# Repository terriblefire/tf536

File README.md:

# TF536

A Motorola 68030-based hardware accelerator for Amiga 500 and CDTV computers. The TF536 provides a modern 68030 CPU upgrade with SDRAM expansion, IDE interface, and custom CPLD logic for bus arbitration and peripheral management.

**Note**: For Atari ST systems, see the ST536 derivative available from [Exxos](https://www.exxosforum.co.uk/).

## Discord

https://discord.gg/Q5zfusgnmH

## Overview

The TF536 is an open-source hardware accelerator that replaces the original 68000 CPU in Amiga 500 and CDTV systems with a faster 68030 processor. The design uses a Xilinx XC95144XL/XC95288XL CPLD to implement:

- Bus arbitration between 68030 and host system
- SDRAM controller with Amiga autoconfig support
- IDE/ATA interface (Amiga Gayle chipset emulation)
- 68000 peripheral bus timing (6800-style VPA/VMA)
- Clock generation and speed control
- Interrupt handling and bus error generation

## Features

- **68030 CPU**: Significant performance upgrade from stock 68000
- **SDRAM Expansion**: Up to 128MB of fast RAM via SDRAM controller
- **IDE Interface**: Connect IDE hard drives and CF card adapters
- **Amiga Autoconfig**: Automatic memory configuration (Zorro-II compatible)
- **Multi-Platform**: Support for Amiga 500 and CDTV
- **Boot ROM**: Custom 68k assembly boot code with color cycling demo
- **Hardware Revisions**: Evolution from Rev 1 to Rev 2 with improvements
- **Automated Manufacturing**: Complete Gerber, BOM, and CPL generation

## Supported Platforms

The TF536 firmware supports two different target platforms, selected at compile time:

- **A500**: Amiga 500 configuration
- **CDTV**: Commodore CDTV configuration (different ROM decode)

Each platform has specific CPLD defines (`A500`, `CDTV`) that customize the memory map and bus interface behavior.

## Hardware Revisions

### Revision 2 (Current)
The current repository contains the **Rev 2** design (`boards/tf536r2/`), which includes:
- 4-layer PCB design
- Improved signal integrity
- JLCPCB-compatible manufacturing outputs
- Both top and bottom component placement
- Configurable IDE interface (buffered or unbuffered)

### Revision 1
Legacy design available in `boards/tf536r1/` with earlier schematic iterations.

## IDE Interface Build Options

The TF536 supports two mutually exclusive IDE interface configurations:

- **Unbuffered (Default)**: Populate RN5-RN10 with 0Ω resistor networks
- **Buffered**: Populate IC4, IC5, IC6 with buffer ICs

⚠️ **Important**: Do not populate both options simultaneously.

See [IDE_BUILD_OPTIONS.md](IDE_BUILD_OPTIONS.md) for detailed information on choosing and assembling the appropriate configuration.

## Repository Structure

```
tf536/
├── rtl/                    # Verilog RTL source code
│   ├── main_top.v         # Top-level CPLD module (parametric)
│   ├── clocks.v           # Clock generation and CPU speed control
│   ├── sdram.v            # SDRAM controller with burst support
│   ├── sdram_init.v       # SDRAM initialization state machine
│   ├── autoconfig.v       # Amiga Zorro-II autoconfiguration
│   ├── bus.v              # Bus delay and arbitration logic
│   ├── m6800.v            # Motorola 6800 peripheral bus timing
│   ├── ata.v              # IDE/ATA interface controller
│   ├── gayle.v            # Amiga Gayle IDE chipset emulation
│   ├── interrupt.v        # Interrupt level management
│   ├── intreqr.v          # Interrupt request register patching
│   └── bootrom.v          # Boot ROM (auto-generated from assembly)
├── rom/                    # Boot ROM assembly source
│   ├── bootrom.asm        # 68k assembly boot code
│   ├── bin2vrlg           # Binary to Verilog converter (Python 3)
│   └── Makefile           # ROM build automation
├── boards/                 # Board-specific build configurations
│   ├── tf536r1/           # Revision 1 board files
│   ├── tf536r2/           # Revision 2 board files (current)
│   │   ├── tf536r2_main_top.v  # Board-specific wrapper
│   │   ├── tf536r2_main.ucf    # Pin constraints
│   │   └── Makefile            # Build targets (a500, cdtv, atarist)
│   ├── Makefile.cpld      # Common CPLD synthesis rules
│   ├── Makefile.inc       # Docker/Xilinx environment setup
│   └── boards.txt         # List of board configurations
├── testsuite/             # Verilog testbenches
│   ├── bus/               # Bus interface tests
│   ├── interrupt/         # Interrupt handling tests
│   └── Makefile.inc       # Common test environment
├── eagle/                 # Eagle CAD hardware designs
│   ├── tf536.sch          # Schematic (3 sheets)
│   ├── tf536.brd          # PCB layout (4-layer)
│   ├── extract_bom.py     # BOM extraction (JLCPCB format)
│   ├── extract_cpl.py     # Component placement list
│   ├── jlcpcb_4_layer_v9.cam  # Gerber generation CAM job
│   └── Makefile           # Automated manufacturing outputs
└── .github/workflows/     # CI/CD automation
    ├── build-firmware.yml     # CPLD firmware builds
    ├── gerbers.yml            # Gerber file generation
    ├── schematic-pdf.yml      # PDF schematic generation
    └── generate_assembly.yml  # BOM and CPL generation
```

## Building the CPLD Firmware

### Prerequisites

- **Linux**: Xilinx ISE 10.1 installed at `/opt/Xilinx/10.1/`
- **macOS/Windows**: Docker (automatically uses terriblefire78/xilinx:v1 container)
- **68k Assembly**: vasmm68k_mot assembler for boot ROM

The build system automatically handles Docker on non-Linux platforms.

### Build Boot ROM

```bash
cd rom
make
```

Generates `bootrom.v` from `bootrom.asm` with embedded version string.

### Build All Platforms

```bash
cd boards/tf536r2
make
```

This compiles CPLD firmware for both platforms using the XC95288XL CPLD:
- `tf536r2_main_top_A500_XC95288XL_PHASE_7.jed` (Amiga 500)
- `tf536r2_main_top_CDTV_XC95288XL_PHASE_7.jed` (CDTV)

### Build Specific Platform

```bash
cd boards/tf536r2
make a500      # Amiga 500
make cdtv      # Commodore CDTV
```

Output: `.jed` (JEDEC programming files) and `.svf` (Serial Vector Format)

### Build Configuration

Key Makefile variables (used internally by `boards/tf536r2/Makefile`):

```makefile
CHIPSIZE=288        # XC95288XL CPLD
CLOCK_PHASE=7       # Clock phase alignment (0-7)
TARGET=A500         # Platform target (A500, CDTV)
```

### Clean Build Artifacts

```bash
cd boards
make clean       # Remove intermediate files, keep .jed
make distclean   # Remove all generated files including .jed
```

### Create Release Package

```bash
cd boards
make zip
```

Generates: `tf536_YYYY_MM_DD_<git-hash>.zip` containing all board `.jed` files.

## Hardware Manufacturing

### Generate Gerber Files

```bash
cd eagle
make gerbers
```

Output: `tf536_<git>_<date>.zip` containing complete 4-layer PCB fabrication package for JLCPCB.

### Generate PDF Schematic

```bash
cd eagle
make pdf
```

Output: `tf536_<git>_<date>.pdf` - Multi-page PDF schematic (3 sheets)

### Generate Assembly Files

```bash
cd eagle
make assembly
```

Generates:
- `tf536_bom.csv` - Bill of Materials (JLCPCB format)
- `tf536_cpl.csv` - Component Placement List for SMT assembly

### Complete Manufacturing Output

```bash
cd eagle
make all         # Gerber files + ZIP
make bom         # Bill of Materials only
make cpl         # Component Placement List only
make clean       # Remove all generated files
```

## RTL Architecture

### Module Hierarchy

**Top-level:** `main_top.v` (parametric, instantiated by board-specific wrapper)

**Key Modules:**
- **`clocks.v`**: Clock management, CPU speed control, 7MHz/100MHz domain crossing
- **`sdram.v`**: SDRAM controller with burst read/write, refresh, autoconfig decode
- **`sdram_init.v`**: SDRAM initialization (precharge, auto-refresh, mode register)
- **`autoconfig.v`**: Amiga Zorro-II autoconfiguration protocol
- **`bus.v`**: Bus delay state machine and control
- **`m6800.v`**: Motorola 6800 peripheral bus timing (VPA/VMA/E-clock)
- **`ata.v`**: IDE/ATA interface with wait state generation
- **`gayle.v`**: Amiga Gayle chipset emulation (IDE interrupt, status)
- **`interrupt.v`**: IPL interrupt level assertion and acknowledgment
- **`intreqr.v`**: INTREQ/INTENA register patching for IDE interrupts
- **`bootrom.v`**: Boot ROM lookup table (auto-generated from assembly)

### Design Patterns

- **Dual-clock design**: CLK7M (7MHz Amiga bus) and CLK100M (system/SDRAM)
- **Bus punting**: Decides when to drive Amiga bus vs. tri-state (HIGHZ)
- **Platform-specific compilation**: `ifdef` directives for A500/CDTV
- **DSACK protocol**: Variable wait state insertion for fast RAM access
- **Cache support**: CBREQ/CBACK/CIIN signals for 68030 cache control

### Memory Map

**Amiga Configuration:**
- `$00000000-$001FFFFF`: Chip RAM (host)
- `$00200000-$009FFFFF`: Autoconfig space
- `$00A00000-$00BFFFFF`: Reserved (CIA, Custom chips)
- `$00C00000-$00DFFFFF`: Slow RAM (host)
- `$00E00000-$00E7FFFF`: Autoconfig ROM
- `$00F00000-$00F7FFFF`: Cartridge ROM (unless CDTV)
- `$00F80000-$00FFFFFF`: System ROM (Kickstart)
- `$01000000+`: Fast RAM (SDRAM, autoconfigured)

**CDTV Configuration:**
- ROM decode disabled at `$00F00000` (see `main_top.v:268-272`)

## Testing

Run Verilog testbenches:

```bash
cd testsuite/interrupt
make

cd testsuite/bus
make
```

Testbenches use Icarus Verilog (iverilog) and follow naming convention `test_*.v`.

## Programming the CPLD

The `.jed` files can be programmed using:
- JTAG programmer (Xilinx Platform Cable, etc.)
- xc3sprog with FT232H-based programmer
- Xilinx iMPACT software

## CI/CD Automation

GitHub Actions automatically builds:
- **CPLD Firmware**: On changes to `rtl/`, `boards/`, or `rom/`
- **Gerber Files**: On push to develop/main branches
- **PDF Schematics**: On push to develop/main branches
- **Assembly Files**: On changes to Eagle files or extraction scripts

All build artifacts are uploaded and available for download for 90 days. Tagged releases automatically include manufacturing outputs.

## License

This work is licensed under the Creative Commons Attribution-NoDerivatives 4.0 International License.

Copyright (c) 2016-2025 Stephen J. Leary

You are free to:
- **Share** - copy and redistribute the material in any medium or format for any purpose, even commercially

Under the following terms:
- **Attribution** - You must give appropriate credit, provide a link to the license, and indicate if changes were made
- **NoDerivatives** - If you remix, transform, or build upon the material, you may not distribute the modified material

See the [LICENSE](LICENSE) file for the complete license text, or visit:
https://creativecommons.org/licenses/by-nd/4.0/

## Community

Join the TerribleFire Discord for support, discussions, and updates: https://discord.gg/aXGkKWJQ

## Credits

- Hardware design: Stephen Leary
- CPLD development: Stephen Leary
- Open source contributions welcome!

---

**Note**: This is a complex hardware project requiring experience with:
- Eagle CAD for hardware modifications
- Verilog HDL for CPLD changes
- 68000/68030 assembly for boot ROM modifications
- Xilinx ISE 10.1 toolchain for CPLD synthesis
- PCB fabrication and SMT assembly services

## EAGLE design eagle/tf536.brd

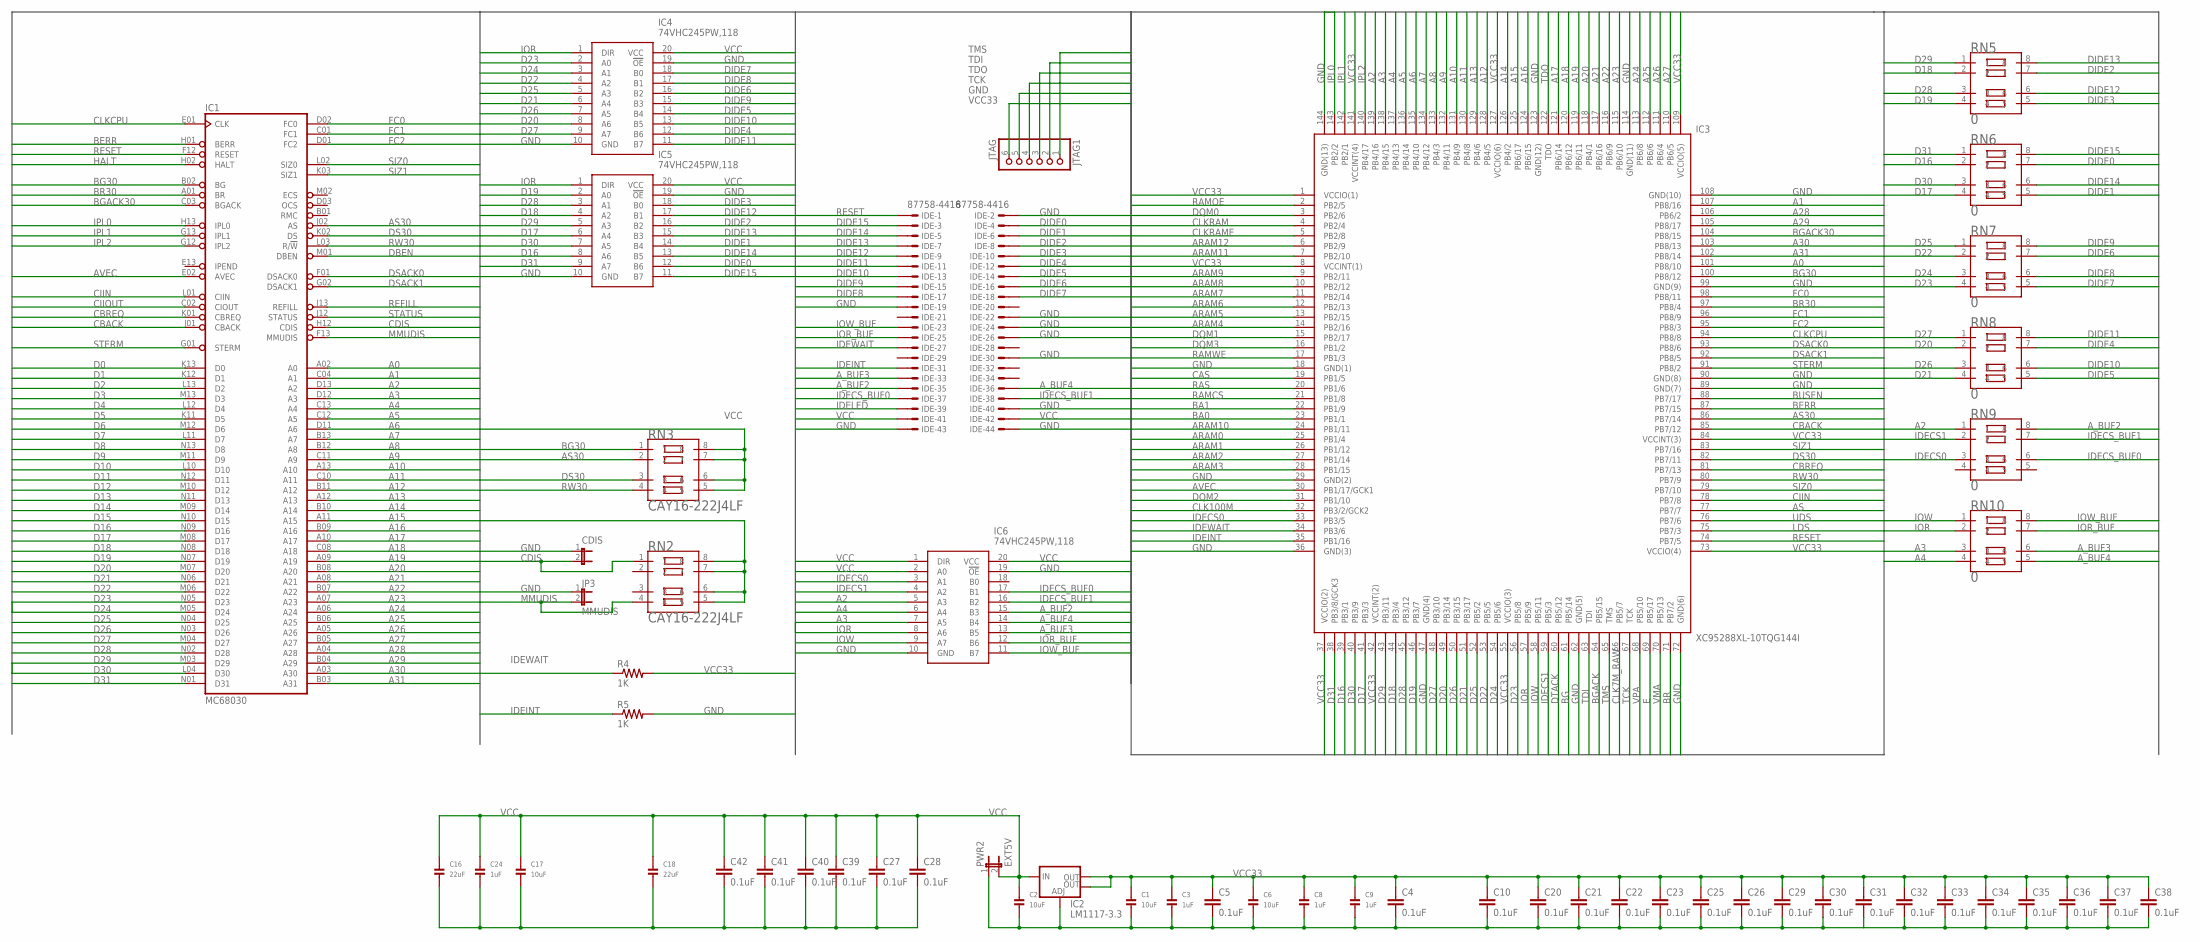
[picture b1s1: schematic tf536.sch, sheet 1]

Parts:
C1, C2, C6, C17: 10uF; 1206
C3, C8, C9, C24: 1uF; 1206
C4, C5, C10, C20, C21, C22, C23, C25, C26, C27, C28, C29, C30, C31, C32, C33, C34, C35, C36, C37, C38, C39, C40, C41, C42: 0.1uF; 0603-CAP
C16, C18: 22uF; 1206
IC1: MC68030; MPGA128
IC2: LM1117-3.3; SOT223
IC3: XC95288XL-10TQG144I; SAMACSYS_PARTS_QFP50P2200X2200X160-144N
IC4, IC5, IC6: 74VHC245PW,118; SOP65P640X110-20N
IDE: 87758-4416
JP3: MMUDIS; 1X02
JP5: CDIS; 1X02
JTAG1: JTAG; 1X06_ROUND
PWR2: EXT5V; 1X02
R4, R5: 1K; 0603
RN2, RN3: CAY16-222J4LF; RESCAXE80P320X160-8N
RN5, RN6, RN7, RN8, RN9, RN10: 0; RESCAXE80P320X160-8N

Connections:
A0: IC1.A02 (A0), IC3.101 (PB8/10)
A1: IC1.C04 (A1), IC3.107 (PB8/16); also elsewhere on the board
A2: IC1.D13 (A2), IC3.139 (PB4/16), IC6.5 (A3), RN9.1; also elsewhere on the board
A3: IC1.D12 (A3), IC3.138 (PB4/15), IC6.7 (A5), RN10.3; also elsewhere on the board
A4: IC1.C13 (A4), IC3.137 (PB4/13), IC6.6 (A4), RN10.4; also elsewhere on the board
A5: IC1.C12 (A5), IC3.136 (PB4/14); also elsewhere on the board
A6: IC1.D11 (A6), IC3.135 (PB4/10); also elsewhere on the board
A7: IC1.B13 (A7), IC3.134 (PB4/12); also elsewhere on the board
A8: IC1.B12 (A8), IC3.133 (PB4/3); also elsewhere on the board
A9: IC1.C11 (A9), IC3.132 (PB4/11); also elsewhere on the board
A10: IC1.A13 (A10), IC3.131 (PB4/9); also elsewhere on the board
A11: IC1.C10 (A11), IC3.130 (PB4/8); also elsewhere on the board
A12: IC1.B11 (A12), IC3.128 (PB4/5); also elsewhere on the board
A13: IC1.A12 (A13), IC3.129 (PB4/6); also elsewhere on the board
A14: IC1.B10 (A14), IC3.126 (PB4/2); also elsewhere on the board
A15: IC1.A11 (A15), IC3.125 (PB6/17); also elsewhere on the board
A16: IC1.B09 (A16), IC3.124 (PB6/15); also elsewhere on the board
A17: IC1.A10 (A17), IC3.121 (PB6/14); also elsewhere on the board
A18: IC1.C08 (A18), IC3.120 (PB6/12); also elsewhere on the board
A19: IC1.A09 (A19), IC3.119 (PB6/11); also elsewhere on the board
A20: IC1.B08 (A20), IC3.118 (PB4/1); also elsewhere on the board
A21: IC1.A08 (A21), IC3.117 (PB6/16); also elsewhere on the board
A22: IC1.B07 (A22), IC3.116 (PB6/9); also elsewhere on the board
A23: IC1.A07 (A23), IC3.115 (PB6/10); also elsewhere on the board
A24: IC1.A06 (A24), IC3.113 (PB6/8); also elsewhere on the board
A25: IC1.B06 (A25), IC3.112 (PB6/6); also elsewhere on the board
A26: IC1.A05 (A26), IC3.111 (PB6/4); also elsewhere on the board
A27: IC1.B05 (A27), IC3.110 (PB6/5); also elsewhere on the board
A28: IC1.A04 (A28), IC3.106 (PB6/2); also elsewhere on the board
A29: IC1.B04 (A29), IC3.105 (PB8/17); also elsewhere on the board
A30: IC1.A03 (A30), IC3.103 (PB8/13); also elsewhere on the board
A31: IC1.B03 (A31), IC3.102 (PB8/14); also elsewhere on the board
ARAM0: IC3.25 (PB1/4); also elsewhere on the board
ARAM1: IC3.26 (PB1/12); also elsewhere on the board
ARAM2: IC3.27 (PB1/14); also elsewhere on the board
ARAM3: IC3.28 (PB1/15); also elsewhere on the board
ARAM4: IC3.14 (PB2/16); also elsewhere on the board
ARAM5: IC3.13 (PB2/15); also elsewhere on the board
ARAM6: IC3.12 (PB2/13); also elsewhere on the board
ARAM7: IC3.11 (PB2/14); also elsewhere on the board
ARAM8: IC3.10 (PB2/12); also elsewhere on the board
ARAM9: IC3.9 (PB2/11); also elsewhere on the board
ARAM10: IC3.24 (PB1/11); also elsewhere on the board
ARAM11: IC3.7 (PB2/10); also elsewhere on the board
ARAM12: IC3.6 (PB2/9); also elsewhere on the board
AS: IC3.77 (PB7/7); also elsewhere on the board
AS30: IC1.J02 (AS), IC3.86 (PB7/14), RN3.2
AVEC: IC1.E02 (AVEC), IC3.30 (PB1/17/GCK1)
A_BUF2: IC6.15 (B3), IDE.35, RN9.8
A_BUF3: IC6.13 (B5), IDE.33, RN10.6
A_BUF4: IC6.14 (B4), IDE.36, RN10.5
BA0: IC3.23 (PB1/1); also elsewhere on the board
BA1: IC3.22 (PB1/9); also elsewhere on the board
BERR: IC1.H01 (BERR), IC3.87 (PB7/15); also elsewhere on the board
BG: IC3.61 (PB5/14); also elsewhere on the board
BG30: IC1.B02 (BG), IC3.100 (PB8/12), RN3.1
BGACK: IC3.64 (PB5/15); also elsewhere on the board
BGACK30: IC1.C03 (BGACK), IC3.104 (PB8/15)
BR: IC3.71 (PB7/2); also elsewhere on the board
BR30: IC1.A01 (BR), IC3.97 (PB8/4)
BUSEN: IC3.88 (PB7/17); also elsewhere on the board
CAS: IC3.19 (PB1/5); also elsewhere on the board
CBACK: IC1.J01 (CBACK), IC3.85 (PB7/12)
CBREQ: IC1.K01 (CBREQ), IC3.81 (PB7/13)
CDIS: IC1.H12 (CDIS), JP5.2, RN2.1
CIIN: IC1.L01 (CIIN), IC3.78 (PB7/8)
CIIOUT: IC1.C02 (CIOUT)
CLK7M_RAW: IC3.66 (PB5/7); also elsewhere on the board
CLK100M: IC3.32 (PB3/2/GCK2); also elsewhere on the board
CLKCPU: IC1.E01 (CLK), IC3.94 (PB8/8)
CLKRAM: IC3.4 (PB2/4); also elsewhere on the board
CLKRAME: IC3.5 (PB2/8); also elsewhere on the board
D0: IC1.K13 (D0); also elsewhere on the board
D1: IC1.K12 (D1); also elsewhere on the board
D2: IC1.L13 (D2); also elsewhere on the board
D3: IC1.M13 (D3); also elsewhere on the board
D4: IC1.L12 (D4); also elsewhere on the board
D5: IC1.K11 (D5); also elsewhere on the board
D6: IC1.M12 (D6); also elsewhere on the board
D7: IC1.L11 (D7); also elsewhere on the board
D8: IC1.N13 (D8); also elsewhere on the board
D9: IC1.M11 (D9); also elsewhere on the board
D10: IC1.L10 (D10); also elsewhere on the board
D11: IC1.N12 (D11); also elsewhere on the board
D12: IC1.M10 (D12); also elsewhere on the board
D13: IC1.N11 (D13); also elsewhere on the board
D14: IC1.M09 (D14); also elsewhere on the board
D15: IC1.N10 (D15); also elsewhere on the board
D16: IC1.N09 (D16), IC3.39 (PB3/1), IC5.8 (A6), RN6.2; also elsewhere on the board
D17: IC1.M08 (D17), IC3.41 (PB3/3), IC5.6 (A4), RN6.4; also elsewhere on the board
D18: IC1.N08 (D18), IC3.44 (PB3/4), IC5.4 (A2), RN5.2; also elsewhere on the board
D19: IC1.N07 (D19), IC3.46 (PB3/7), IC5.2 (A0), RN5.4; also elsewhere on the board
D20: IC1.M07 (D20), IC3.49 (PB3/14), IC4.8 (A6), RN8.2; also elsewhere on the board
D21: IC1.N06 (D21), IC3.51 (PB3/17), IC4.6 (A4), RN8.4; also elsewhere on the board
D22: IC1.M06 (D22), IC3.53 (PB5/5), IC4.4 (A2), RN7.2; also elsewhere on the board
D23: IC1.N05 (D23), IC3.56 (PB5/8), IC4.2 (A0), RN7.4; also elsewhere on the board
D24: IC1.M05 (D24), IC3.54 (PB5/6), IC4.3 (A1), RN7.3; also elsewhere on the board
D25: IC1.N04 (D25), IC3.52 (PB5/2), IC4.5 (A3), RN7.1; also elsewhere on the board
D26: IC1.N03 (D26), IC3.50 (PB3/15), IC4.7 (A5), RN8.3; also elsewhere on the board
D27: IC1.M04 (D27), IC3.48 (PB3/10), IC4.9 (A7), RN8.1; also elsewhere on the board
D28: IC1.N02 (D28), IC3.45 (PB3/12), IC5.3 (A1), RN5.3; also elsewhere on the board
D29: IC1.M03 (D29), IC3.43 (PB3/11), IC5.5 (A3), RN5.1; also elsewhere on the board
D30: IC1.L04 (D30), IC3.40 (PB3/9), IC5.7 (A5), RN6.3; also elsewhere on the board
D31: IC1.N01 (D31), IC3.38 (PB3/8/GCK3), IC5.9 (A7), RN6.1; also elsewhere on the board
DBEN: IC1.M01 (DBEN)
DIDE0: IC5.12 (B6), IDE.4, RN6.7
DIDE1: IC5.14 (B4), IDE.6, RN6.5
DIDE2: IC5.16 (B2), IDE.8, RN5.7
DIDE3: IC5.18 (B0), IDE.10, RN5.5
DIDE4: IC4.12 (B6), IDE.12, RN8.7
DIDE5: IC4.14 (B4), IDE.14, RN8.5
DIDE6: IC4.16 (B2), IDE.16, RN7.7
DIDE7: IC4.18 (B0), IDE.18, RN7.5
DIDE8: IC4.17 (B1), IDE.17, RN7.6
DIDE9: IC4.15 (B3), IDE.15, RN7.8
DIDE10: IC4.13 (B5), IDE.13, RN8.6
DIDE11: IC4.11 (B7), IDE.11, RN8.8
DIDE12: IC5.17 (B1), IDE.9, RN5.6
DIDE13: IC5.15 (B3), IDE.7, RN5.8
DIDE14: IC5.13 (B5), IDE.5, RN6.6
DIDE15: IC5.11 (B7), IDE.3, RN6.8
DQM0: IC3.3 (PB2/6); also elsewhere on the board
DQM1: IC3.15 (PB2/17); also elsewhere on the board
DQM2: IC3.31 (PB1/10); also elsewhere on the board
DQM3: IC3.16 (PB1/2); also elsewhere on the board
DS30: IC1.K02 (DS), IC3.82 (PB7/11), RN3.3
DSACK0: IC1.F01 (DSACK0), IC3.93 (PB8/6)
DSACK1: IC1.G02 (DSACK1), IC3.92 (PB8/5)
DTACK: IC3.60 (PB5/12); also elsewhere on the board
E: IC3.69 (PB5/17); also elsewhere on the board
FC0: IC1.D02 (FC0), IC3.98 (PB8/11); also elsewhere on the board
FC1: IC1.C01 (FC1), IC3.96 (PB8/9); also elsewhere on the board
FC2: IC1.D01 (FC2), IC3.95 (PB8/3); also elsewhere on the board
GND: C1.2, C2.2, C3.2, C4.2, C5.2, C6.2, C8.2, C9.2, C10.2, C16.2, C17.2, C18.2, C20.2, C21.2, C22.2, C23.2, C24.2, C25.2, C26.2, C27.2, C28.2, C29.2, C30.2, C31.2, C32.2, C33.2, C34.2, C35.2, C36.2, C37.2, C38.2, C39.2, C40.2, C41.2, C42.2, IC1.C05 (GND), IC1.C07 (GND), IC1.C09 (GND), IC1.E03 (GND), IC1.E11 (GND), IC1.F03 (GND), IC1.G03 (GND), IC1.G11 (GND), IC1.J03 (GND), IC1.J11 (GND), IC1.L05 (GND), IC1.L07 (GND), IC1.L08 (GND), IC1.L09 (GND), IC2.1 (ADJ), IC3.18 (GND(1)), IC3.29 (GND(2)), IC3.36 (GND(3)), IC3.47 (GND(4)), IC3.62 (GND(5)), IC3.72 (GND(6)), IC3.89 (GND(7)), IC3.90 (GND(8)), IC3.99 (GND(9)), IC3.108 (GND(10)), IC3.114 (GND(11)), IC3.123 (GND(12)), IC3.144 (GND(13)), IC4.10 (GND), IC4.19 (!OE), IC5.10 (GND), IC5.19 (!OE), IC6.10 (GND), IC6.19 (!OE), IDE.2, IDE.19, IDE.22, IDE.24, IDE.26, IDE.30, IDE.40, IDE.43, IDE.44, JP3.1, JP5.1, JTAG1.5, PWR2.1, R5.2; also elsewhere on the board
HALT: IC1.H02 (HALT); also elsewhere on the board
IDECS0: IC3.33 (PB3/5), IC6.3 (A1), RN9.3
IDECS1: IC3.59 (PB5/3), IC6.4 (A2), RN9.2
IDECS_BUF0: IC6.17 (B1), IDE.37, RN9.6
IDECS_BUF1: IC6.16 (B2), IDE.38, RN9.7
IDEINT: IC3.35 (PB1/16), IDE.31, R5.1
IDELED: IDE.39
IDEWAIT: IC3.34 (PB3/6), IDE.27, R4.1
IOR: IC3.57 (PB5/9), IC4.1 (DIR), IC5.1 (DIR), IC6.8 (A6), RN10.2
IOR_BUF: IC6.12 (B6), IDE.25, RN10.7
IOW: IC3.58 (PB5/11), IC6.9 (A7), RN10.1
IOW_BUF: IC6.11 (B7), IDE.23, RN10.8
IPL0: IC1.H13 (IPL0), IC3.143 (PB2/2); also elsewhere on the board
IPL1: IC1.G13 (IPL1), IC3.142 (PB2/1); also elsewhere on the board
IPL2: IC1.G12 (IPL2), IC3.140 (PB4/17); also elsewhere on the board
LDS: IC3.75 (PB7/3); also elsewhere on the board
MMUDIS: IC1.F13 (MMUDIS), JP3.2, RN2.4
RAMCS: IC3.21 (PB1/8); also elsewhere on the board
RAMOE: IC3.2 (PB2/5); also elsewhere on the board
RAMWE: IC3.17 (PB1/3); also elsewhere on the board
RAS: IC3.20 (PB1/6); also elsewhere on the board
REFILL: IC1.J13 (REFILL)
RESET: IC1.F12 (RESET), IC3.74 (PB7/5), IDE.1; also elsewhere on the board
RW30: IC1.L03 (R/!W), IC3.80 (PB7/9), RN3.4; also elsewhere on the board
SIZ0: IC1.L02 (SIZ0), IC3.79 (PB7/10)
SIZ1: IC1.K03 (SIZ1), IC3.83 (PB7/16)
STATUS: IC1.J12 (STATUS)
STERM: IC1.G01 (STERM), IC3.91 (PB8/2)
TCK: IC3.67 (TCK), JTAG1.4
TDI: IC3.63 (TDI), JTAG1.2
TDO: IC3.122 (TDO), JTAG1.3
TMS: IC3.65 (TMS), JTAG1.1
UDS: IC3.76 (PB7/6); also elsewhere on the board
VCC: C2.1, C16.1, C17.1, C18.1, C24.1, C27.1, C28.1, C39.1, C40.1, C41.1, C42.1, IC1.C06 (VCC), IC1.D04 (VCC), IC1.D10 (VCC), IC1.F02 (VCC), IC1.F11 (VCC), IC1.H03 (VCC), IC1.H11 (VCC), IC1.K04 (VCC), IC1.K10 (VCC), IC1.L06 (VCC), IC2.3 (IN), IC4.20 (VCC), IC5.20 (VCC), IC6.1 (DIR), IC6.2 (A0), IC6.20 (VCC), IDE.41, IDE.42, PWR2.2, RN3.5, RN3.6, RN3.7, RN3.8; also elsewhere on the board
VCC33: C1.1, C3.1, C4.1, C5.1, C6.1, C8.1, C9.1, C10.1, C20.1, C21.1, C22.1, C23.1, C25.1, C26.1, C29.1, C30.1, C31.1, C32.1, C33.1, C34.1, C35.1, C36.1, C37.1, C38.1, IC2.2 (OUT), IC2.4 (OUT), IC3.1 (VCCIO(1)), IC3.8 (VCCINT(1)), IC3.37 (VCCIO(2)), IC3.42 (VCCINT(2)), IC3.55 (VCCIO(3)), IC3.73 (VCCIO(4)), IC3.84 (VCCINT(3)), IC3.109 (VCCIO(5)), IC3.127 (VCCIO(6)), IC3.141 (VCCINT(4)), JTAG1.6, R4.2, RN2.5, RN2.6, RN2.7, RN2.8; also elsewhere on the board
VMA: IC3.70 (PB5/13); also elsewhere on the board
VPA: IC3.68 (PB5/10); also elsewhere on the board

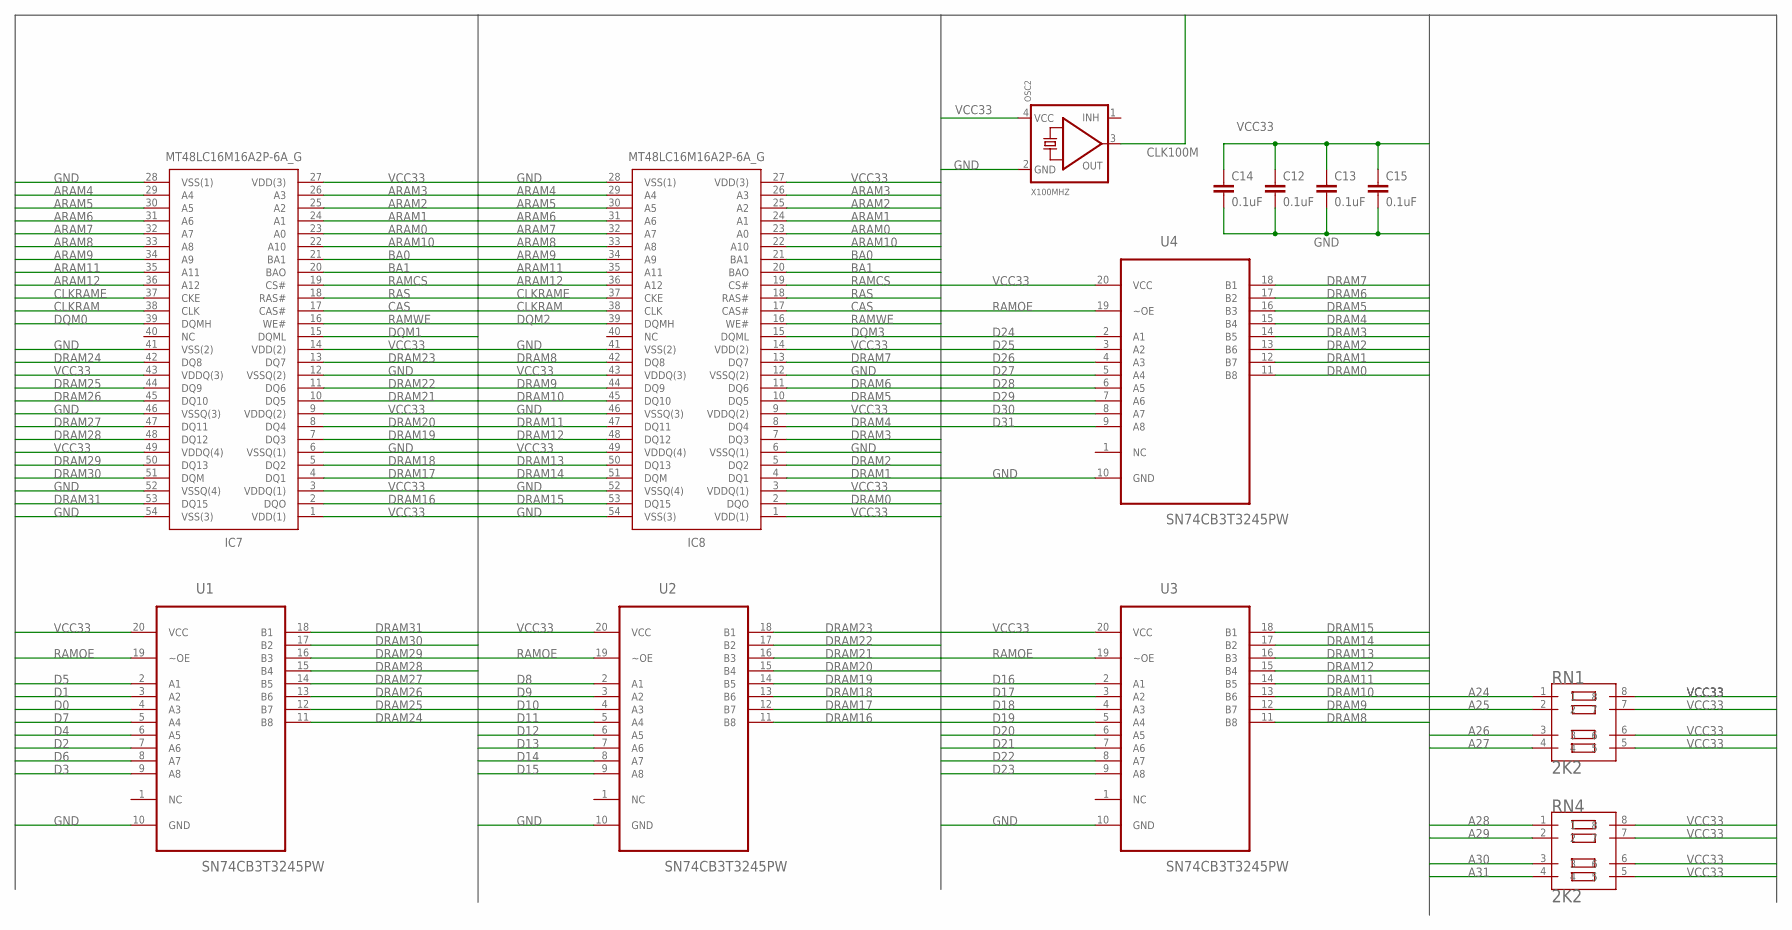
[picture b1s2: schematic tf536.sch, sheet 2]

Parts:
C12, C13, C14, C15: 0.1uF; 0603-CAP
IC7, IC8: MT48LC16M16A2P-6A_G; SOP80P1176X120-54N
OSC2: X100MHZ; OSC_7X5MM
RN1, RN4: 2K2; RESCAXE80P320X160-8N
U1, U2, U3, U4: SN74CB3T3245PW; SOP65P640X120-20N

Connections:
A24: RN1.1; also elsewhere on the board
A25: RN1.2; also elsewhere on the board
A26: RN1.3; also elsewhere on the board
A27: RN1.4; also elsewhere on the board
A28: RN4.1; also elsewhere on the board
A29: RN4.2; also elsewhere on the board
A30: RN4.3; also elsewhere on the board
A31: RN4.4; also elsewhere on the board
ARAM0: IC7.23 (A0), IC8.23 (A0); also elsewhere on the board
ARAM1: IC7.24 (A1), IC8.24 (A1); also elsewhere on the board
ARAM2: IC7.25 (A2), IC8.25 (A2); also elsewhere on the board
ARAM3: IC7.26 (A3), IC8.26 (A3); also elsewhere on the board
ARAM4: IC7.29 (A4), IC8.29 (A4); also elsewhere on the board
ARAM5: IC7.30 (A5), IC8.30 (A5); also elsewhere on the board
ARAM6: IC7.31 (A6), IC8.31 (A6); also elsewhere on the board
ARAM7: IC7.32 (A7), IC8.32 (A7); also elsewhere on the board
ARAM8: IC7.33 (A8), IC8.33 (A8); also elsewhere on the board
ARAM9: IC7.34 (A9), IC8.34 (A9); also elsewhere on the board
ARAM10: IC7.22 (A10), IC8.22 (A10); also elsewhere on the board
ARAM11: IC7.35 (A11), IC8.35 (A11); also elsewhere on the board
ARAM12: IC7.36 (A12), IC8.36 (A12); also elsewhere on the board
BA0: IC7.21 (BA1), IC8.21 (BA1); also elsewhere on the board
BA1: IC7.20 (BAO), IC8.20 (BAO); also elsewhere on the board
CAS: IC7.17 (CAS#), IC8.17 (CAS#); also elsewhere on the board
CLK100M: OSC2.3 (OUT); also elsewhere on the board
CLKRAM: IC7.38 (CLK), IC8.38 (CLK); also elsewhere on the board
CLKRAME: IC7.37 (CKE), IC8.37 (CKE); also elsewhere on the board
D0: U1.4 (A3); also elsewhere on the board
D1: U1.3 (A2); also elsewhere on the board
D2: U1.7 (A6); also elsewhere on the board
D3: U1.9 (A8); also elsewhere on the board
D4: U1.6 (A5); also elsewhere on the board
D5: U1.2 (A1); also elsewhere on the board
D6: U1.8 (A7); also elsewhere on the board
D7: U1.5 (A4); also elsewhere on the board
D8: U2.2 (A1); also elsewhere on the board
D9: U2.3 (A2); also elsewhere on the board
D10: U2.4 (A3); also elsewhere on the board
D11: U2.5 (A4); also elsewhere on the board
D12: U2.6 (A5); also elsewhere on the board
D13: U2.7 (A6); also elsewhere on the board
D14: U2.8 (A7); also elsewhere on the board
D15: U2.9 (A8); also elsewhere on the board
D16: U3.2 (A1); also elsewhere on the board
D17: U3.3 (A2); also elsewhere on the board
D18: U3.4 (A3); also elsewhere on the board
D19: U3.5 (A4); also elsewhere on the board
D20: U3.6 (A5); also elsewhere on the board
D21: U3.7 (A6); also elsewhere on the board
D22: U3.8 (A7); also elsewhere on the board
D23: U3.9 (A8); also elsewhere on the board
D24: U4.2 (A1); also elsewhere on the board
D25: U4.3 (A2); also elsewhere on the board
D26: U4.4 (A3); also elsewhere on the board
D27: U4.5 (A4); also elsewhere on the board
D28: U4.6 (A5); also elsewhere on the board
D29: U4.7 (A6); also elsewhere on the board
D30: U4.8 (A7); also elsewhere on the board
D31: U4.9 (A8); also elsewhere on the board
DQM0: IC7.39 (DQMH); also elsewhere on the board
DQM1: IC7.15 (DQML); also elsewhere on the board
DQM2: IC8.39 (DQMH); also elsewhere on the board
DQM3: IC8.15 (DQML); also elsewhere on the board
DRAM0: IC8.2 (DQO), U4.11 (B8)
DRAM1: IC8.4 (DQ1), U4.12 (B7)
DRAM2: IC8.5 (DQ2), U4.13 (B6)
DRAM3: IC8.7 (DQ3), U4.14 (B5)
DRAM4: IC8.8 (DQ4), U4.15 (B4)
DRAM5: IC8.10 (DQ5), U4.16 (B3)
DRAM6: IC8.11 (DQ6), U4.17 (B2)
DRAM7: IC8.13 (DQ7), U4.18 (B1)
DRAM8: IC8.42 (DQ8), U3.11 (B8)
DRAM9: IC8.44 (DQ9), U3.12 (B7)
DRAM10: IC8.45 (DQ10), U3.13 (B6)
DRAM11: IC8.47 (DQ11), U3.14 (B5)
DRAM12: IC8.48 (DQ12), U3.15 (B4)
DRAM13: IC8.50 (DQ13), U3.16 (B3)
DRAM14: IC8.51 (DQM), U3.17 (B2)
DRAM15: IC8.53 (DQ15), U3.18 (B1)
DRAM16: IC7.2 (DQO), U2.11 (B8)
DRAM17: IC7.4 (DQ1), U2.12 (B7)
DRAM18: IC7.5 (DQ2), U2.13 (B6)
DRAM19: IC7.7 (DQ3), U2.14 (B5)
DRAM20: IC7.8 (DQ4), U2.15 (B4)
DRAM21: IC7.10 (DQ5), U2.16 (B3)
DRAM22: IC7.11 (DQ6), U2.17 (B2)
DRAM23: IC7.13 (DQ7), U2.18 (B1)
DRAM24: IC7.42 (DQ8), U1.11 (B8)
DRAM25: IC7.44 (DQ9), U1.12 (B7)
DRAM26: IC7.45 (DQ10), U1.13 (B6)
DRAM27: IC7.47 (DQ11), U1.14 (B5)
DRAM28: IC7.48 (DQ12), U1.15 (B4)
DRAM29: IC7.50 (DQ13), U1.16 (B3)
DRAM30: IC7.51 (DQM), U1.17 (B2)
DRAM31: IC7.53 (DQ15), U1.18 (B1)
GND: C12.2, C13.2, C14.2, C15.2, IC7.6 (VSSQ(1)), IC7.12 (VSSQ(2)), IC7.28 (VSS(1)), IC7.41 (VSS(2)), IC7.46 (VSSQ(3)), IC7.52 (VSSQ(4)), IC7.54 (VSS(3)), IC8.6 (VSSQ(1)), IC8.12 (VSSQ(2)), IC8.28 (VSS(1)), IC8.41 (VSS(2)), IC8.46 (VSSQ(3)), IC8.52 (VSSQ(4)), IC8.54 (VSS(3)), OSC2.2 (GND), U1.10 (GND), U2.10 (GND), U3.10 (GND), U4.10 (GND); also elsewhere on the board
RAMCS: IC7.19 (CS#), IC8.19 (CS#); also elsewhere on the board
RAMOE: U1.19 (~OE), U2.19 (~OE), U3.19 (~OE), U4.19 (~OE); also elsewhere on the board
RAMWE: IC7.16 (WE#), IC8.16 (WE#); also elsewhere on the board
RAS: IC7.18 (RAS#), IC8.18 (RAS#); also elsewhere on the board
VCC33: C12.1, C13.1, C14.1, C15.1, IC7.1 (VDD(1)), IC7.3 (VDDQ(1)), IC7.9 (VDDQ(2)), IC7.14 (VDD(2)), IC7.27 (VDD(3)), IC7.43 (VDDQ(3)), IC7.49 (VDDQ(4)), IC8.1 (VDD(1)), IC8.3 (VDDQ(1)), IC8.9 (VDDQ(2)), IC8.14 (VDD(2)), IC8.27 (VDD(3)), IC8.43 (VDDQ(3)), IC8.49 (VDDQ(4)), OSC2.4 (VCC), RN1.5, RN1.6, RN1.7, RN1.8, RN4.5, RN4.6, RN4.7, RN4.8, U1.20 (VCC), U2.20 (VCC), U3.20 (VCC), U4.20 (VCC); also elsewhere on the board

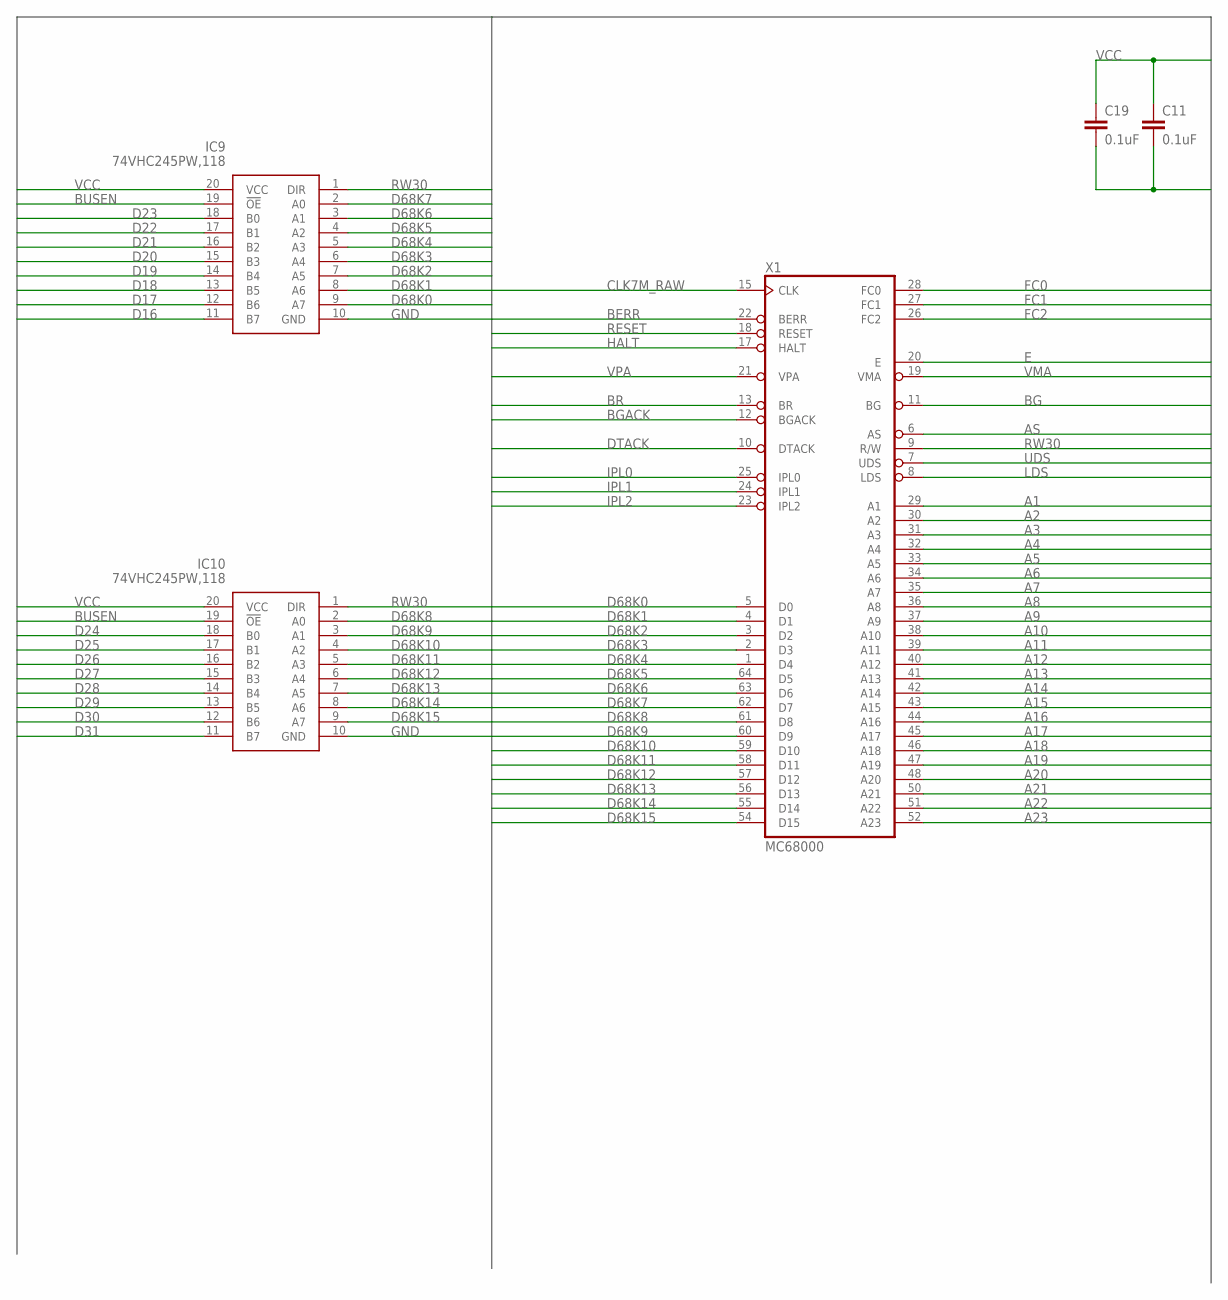
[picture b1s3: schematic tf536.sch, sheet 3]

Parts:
C11, C19: 0.1uF; 0603-CAP
IC9, IC10: 74VHC245PW,118; SOP65P640X110-20N
X1: MC68000; DIL64

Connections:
A1: X1.29 (A1); also elsewhere on the board
A2: X1.30 (A2); also elsewhere on the board
A3: X1.31 (A3); also elsewhere on the board
A4: X1.32 (A4); also elsewhere on the board
A5: X1.33 (A5); also elsewhere on the board
A6: X1.34 (A6); also elsewhere on the board
A7: X1.35 (A7); also elsewhere on the board
A8: X1.36 (A8); also elsewhere on the board
A9: X1.37 (A9); also elsewhere on the board
A10: X1.38 (A10); also elsewhere on the board
A11: X1.39 (A11); also elsewhere on the board
A12: X1.40 (A12); also elsewhere on the board
A13: X1.41 (A13); also elsewhere on the board
A14: X1.42 (A14); also elsewhere on the board
A15: X1.43 (A15); also elsewhere on the board
A16: X1.44 (A16); also elsewhere on the board
A17: X1.45 (A17); also elsewhere on the board
A18: X1.46 (A18); also elsewhere on the board
A19: X1.47 (A19); also elsewhere on the board
A20: X1.48 (A20); also elsewhere on the board
A21: X1.50 (A21); also elsewhere on the board
A22: X1.51 (A22); also elsewhere on the board
A23: X1.52 (A23); also elsewhere on the board
AS: X1.6 (AS); also elsewhere on the board
BERR: X1.22 (BERR); also elsewhere on the board
BG: X1.11 (BG); also elsewhere on the board
BGACK: X1.12 (BGACK); also elsewhere on the board
BR: X1.13 (BR); also elsewhere on the board
BUSEN: IC9.19 (!OE), IC10.19 (!OE); also elsewhere on the board
CLK7M_RAW: X1.15 (CLK); also elsewhere on the board
D16: IC9.11 (B7); also elsewhere on the board
D17: IC9.12 (B6); also elsewhere on the board
D18: IC9.13 (B5); also elsewhere on the board
D19: IC9.14 (B4); also elsewhere on the board
D20: IC9.15 (B3); also elsewhere on the board
D21: IC9.16 (B2); also elsewhere on the board
D22: IC9.17 (B1); also elsewhere on the board
D23: IC9.18 (B0); also elsewhere on the board
D24: IC10.18 (B0); also elsewhere on the board
D25: IC10.17 (B1); also elsewhere on the board
D26: IC10.16 (B2); also elsewhere on the board
D27: IC10.15 (B3); also elsewhere on the board
D28: IC10.14 (B4); also elsewhere on the board
D29: IC10.13 (B5); also elsewhere on the board
D30: IC10.12 (B6); also elsewhere on the board
D31: IC10.11 (B7); also elsewhere on the board
D68K0: IC9.9 (A7), X1.5 (D0)
D68K1: IC9.8 (A6), X1.4 (D1)
D68K2: IC9.7 (A5), X1.3 (D2)
D68K3: IC9.6 (A4), X1.2 (D3)
D68K4: IC9.5 (A3), X1.1 (D4)
D68K5: IC9.4 (A2), X1.64 (D5)
D68K6: IC9.3 (A1), X1.63 (D6)
D68K7: IC9.2 (A0), X1.62 (D7)
D68K8: IC10.2 (A0), X1.61 (D8)
D68K9: IC10.3 (A1), X1.60 (D9)
D68K10: IC10.4 (A2), X1.59 (D10)
D68K11: IC10.5 (A3), X1.58 (D11)
D68K12: IC10.6 (A4), X1.57 (D12)
D68K13: IC10.7 (A5), X1.56 (D13)
D68K14: IC10.8 (A6), X1.55 (D14)
D68K15: IC10.9 (A7), X1.54 (D15)
DTACK: X1.10 (DTACK); also elsewhere on the board
E: X1.20 (E); also elsewhere on the board
FC0: X1.28 (FC0); also elsewhere on the board
FC1: X1.27 (FC1); also elsewhere on the board
FC2: X1.26 (FC2); also elsewhere on the board
GND: C11.2, C19.2, IC9.10 (GND), IC10.10 (GND), X1.16 (GND), X1.53 (GND); also elsewhere on the board
HALT: X1.17 (HALT); also elsewhere on the board
IPL0: X1.25 (IPL0); also elsewhere on the board
IPL1: X1.24 (IPL1); also elsewhere on the board
IPL2: X1.23 (IPL2); also elsewhere on the board
LDS: X1.8 (LDS); also elsewhere on the board
RESET: X1.18 (RESET); also elsewhere on the board
RW30: IC9.1 (DIR), IC10.1 (DIR), X1.9 (R/W); also elsewhere on the board
UDS: X1.7 (UDS); also elsewhere on the board
VCC: C11.1, C19.1, IC9.20 (VCC), IC10.20 (VCC), X1.14 (VCC), X1.49 (VCC); also elsewhere on the board
VMA: X1.19 (VMA); also elsewhere on the board
VPA: X1.21 (VPA); also elsewhere on the board

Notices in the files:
eagle/tf536.brd:
(C) 2019 S.J Leary
parts and their libraries:
microbuilder: This work is placed in the public domain, and may be freely used for commercial and non-commercial work with the following conditions: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
SparkFun-Retired: Licensing:Creative Commons ShareAlike 4.0 International - https://creativecommons.org/licenses/by-sa/4.0
